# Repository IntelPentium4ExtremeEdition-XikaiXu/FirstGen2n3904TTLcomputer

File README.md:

# FirstGen2n3904TTLcomputer
This is a pure homebrew computer designed by Jack and workround and implimented by Cyber guy

10/14/2025-:17: revision 0 is implimented and ready on the dec

//conversation with GROK:

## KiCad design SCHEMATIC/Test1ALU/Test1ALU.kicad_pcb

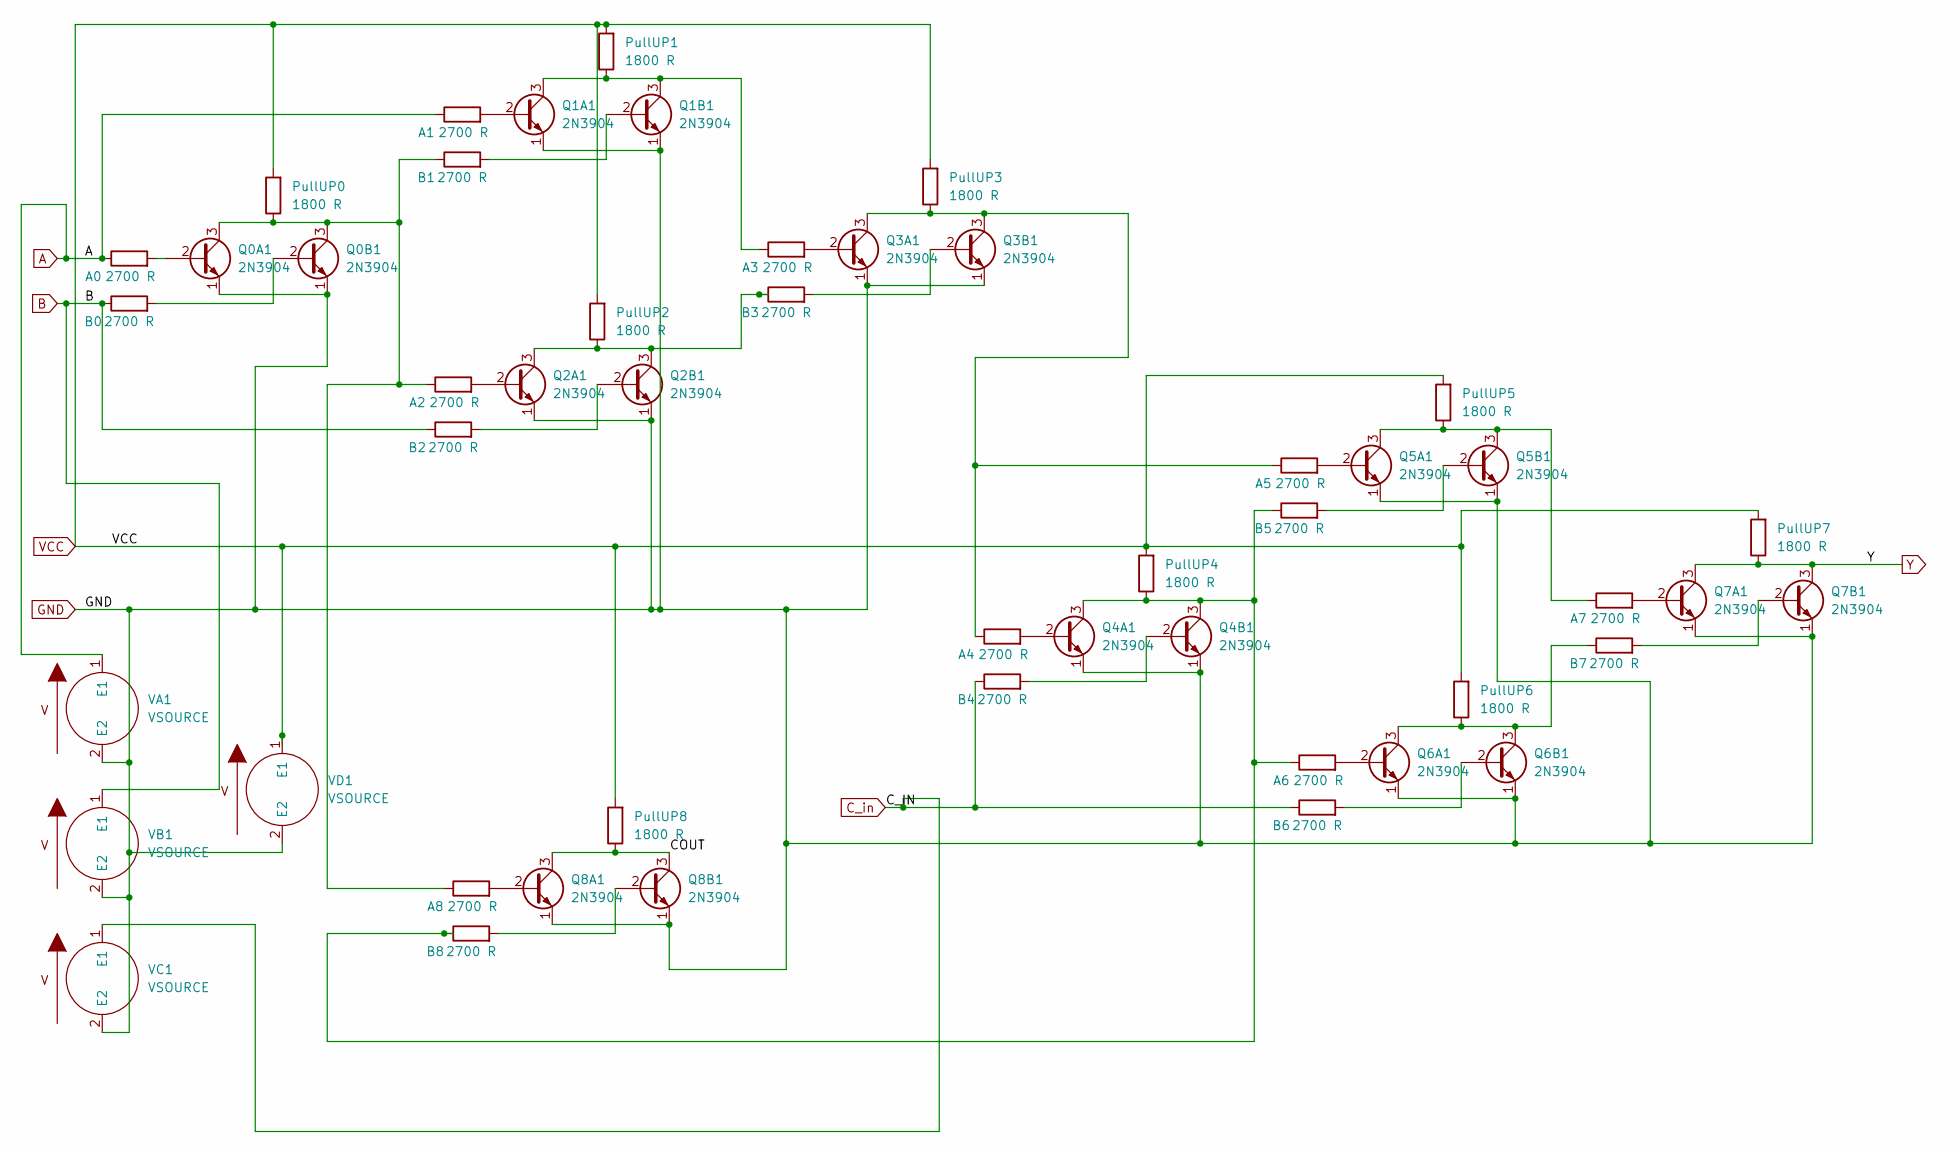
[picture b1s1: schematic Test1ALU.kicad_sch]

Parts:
A0, A1, A2, A3, A4, A5, A6, A7, A8: 2700 R; R_Axial_DIN0204_L3.6mm_D1.6mm_P7.62mm_Horizontal
B0, B1, B2, B3, B4, B5, B6, B7, B8: 2700 R; R_Axial_DIN0204_L3.6mm_D1.6mm_P7.62mm_Horizontal
PullUP0, PullUP1, PullUP2, PullUP3, PullUP4, PullUP5, PullUP6, PullUP7, PullUP8: 1800 R; R_Axial_DIN0204_L3.6mm_D1.6mm_P7.62mm_Horizontal
Q0A1, Q0B1, Q1A1, Q1B1, Q2A1, Q2B1, Q3A1, Q3B1, Q4A1, Q4B1, Q5A1, Q5B1, Q6A1, Q6B1, Q7A1, Q7B1, Q8A1, Q8B1: 2N3904; TO-92_Inline
VA1: VSOURCE
VB1: VSOURCE
VC1: VSOURCE
VD1: VSOURCE

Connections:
A: A0.1, A1.1, VA1.1 (E1)
B: B0.1, B2.1, VB1.1 (E1)
C_in: B4.1, B6.1, VC1.1 (E1)
GND: Q0A1.1 (E), Q0B1.1 (E), Q1A1.1 (E), Q1B1.1 (E), Q2A1.1 (E), Q2B1.1 (E), Q3A1.1 (E), Q3B1.1 (E), Q4A1.1 (E), Q4B1.1 (E), Q5A1.1 (E), Q5B1.1 (E), Q6A1.1 (E), Q6B1.1 (E), Q7A1.1 (E), Q7B1.1 (E), Q8A1.1 (E), Q8B1.1 (E), VA1.2 (E2), VB1.2 (E2), VC1.2 (E2), VD1.2 (E2)
unnamed: A0.2, Q0A1.2 (B)
unnamed: A1.2, Q1A1.2 (B)
unnamed: A2.2, Q2A1.2 (B)
unnamed: A3.2, Q3A1.2 (B)
unnamed: A4.2, Q4A1.2 (B)
unnamed: A5.2, Q5A1.2 (B)
unnamed: A6.2, Q6A1.2 (B)
unnamed: A7.2, Q7A1.2 (B)
unnamed: A8.2, Q8A1.2 (B)
unnamed: B0.2, Q0B1.2 (B)
unnamed: B1.2, Q1B1.2 (B)
unnamed: B2.2, Q2B1.2 (B)
unnamed: B3.2, Q3B1.2 (B)
unnamed: B4.2, Q4B1.2 (B)
unnamed: B5.2, Q5B1.2 (B)
unnamed: B6.2, Q6B1.2 (B)
unnamed: B7.2, Q7B1.2 (B)
unnamed: B8.2, Q8B1.2 (B)
unnamed: A2.1, A8.1, B1.1, PullUP0.1, Q0A1.3 (C), Q0B1.3 (C)
unnamed: A7.1, PullUP5.1, Q5A1.3 (C), Q5B1.3 (C)
unnamed: A3.1, PullUP1.1, Q1A1.3 (C), Q1B1.3 (C)
unnamed: B3.1, PullUP2.1, Q2A1.3 (C), Q2B1.3 (C)
unnamed: A4.1, A5.1, PullUP3.1, Q3A1.3 (C), Q3B1.3 (C)
unnamed: A6.1, B5.1, B8.1, PullUP4.1, Q4A1.3 (C), Q4B1.3 (C)
unnamed: B7.1, PullUP6.1, Q6A1.3 (C), Q6B1.3 (C)
unnamed: PullUP8.1, Q8A1.3 (C), Q8B1.3 (C)
VCC: PullUP0.2, PullUP1.2, PullUP2.2, PullUP3.2, PullUP4.2, PullUP5.2, PullUP6.2, PullUP7.2, PullUP8.2, VD1.1 (E1)
Y: PullUP7.1, Q7A1.3 (C), Q7B1.3 (C)

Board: 2 copper layers, 45 parts (0 on the bottom side), 32 nets, no tracks yet.

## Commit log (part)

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2025-10-14 initial framework built and simulated by the C
2025-10-14 first implimentation
2025-10-14 merging the ram addr to sram single chip
2025-10-14 bit changes
2025-10-19 instrcution change
2025-12-27 KiCAD project created
2026-01-02 test
2026-01-12 RTL Simultation is based
2026-01-28 ALU PROGRESS
2026-01-28 Fixing reg B unloaded issue, now with accu reg
2026-01-28 The progress
2026-02-07 Almost passing the RTL design
2026-02-18 Arch update; from 8 bit to 3 bit inst, 5 bit data
2026-02-18 half_way
2026-02-18 add discription
2026-04-07 Mass mount of changes which lead-in the Homebrew ROM and sram
2026-04-07 rebuild the structure
2026-04-16 ready
2026-04-16 C_sim is ready
2026-04-16 HAHAHAHAH
2026-04-16 Test CP1
